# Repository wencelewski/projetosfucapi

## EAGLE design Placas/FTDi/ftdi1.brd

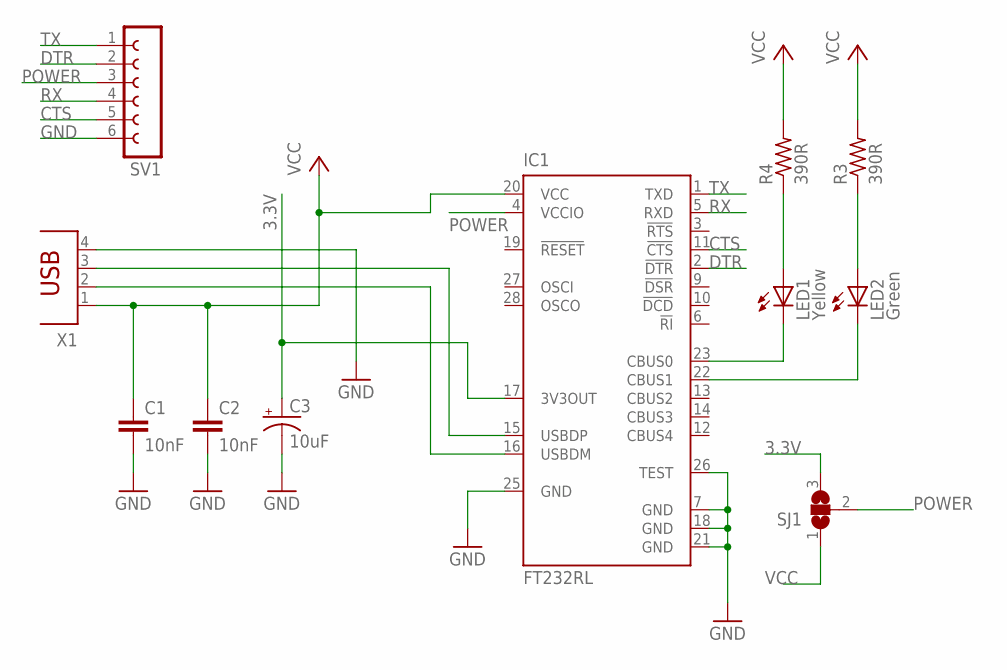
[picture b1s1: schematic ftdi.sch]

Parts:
C1, C2: 10nF; C0805
C3: 10uF; E2,5-6
IC1: FT232RL; SSOP28
LED1: Yellow; LED5MM
LED2: Green; LED5MM
R3, R4: 390R; R0805
SJ1: SJ2W; SJ_2
SV1: FE06-1; FE06
X1: PN87520

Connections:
3.3V: C3.+, IC1.17 (3V3OUT), SJ1.3
CTS: IC1.11 (!CTS), SV1.5
DTR: IC1.2 (!DTR), SV1.2
GND: C1.2, C2.2, C3.-, IC1.7 (GND), IC1.18 (GND), IC1.21 (GND), IC1.25 (GND), IC1.26 (TEST), SV1.6, X1.4
unnamed: IC1.23 (CBUS0), LED1.K (C)
unnamed: IC1.22 (CBUS1), LED2.K (C)
unnamed: LED2.A, R3.1
unnamed: LED1.A, R4.1
unnamed: IC1.16 (USBDM), X1.2
unnamed: IC1.15 (USBDP), X1.3
POWER: IC1.4 (VCCIO), SJ1.2, SV1.3
RX: IC1.5 (RXD), SV1.4
TX: IC1.1 (TXD), SV1.1
VCC: C1.1, C2.1, IC1.20 (VCC), R3.2, R4.2, SJ1.1, X1.1

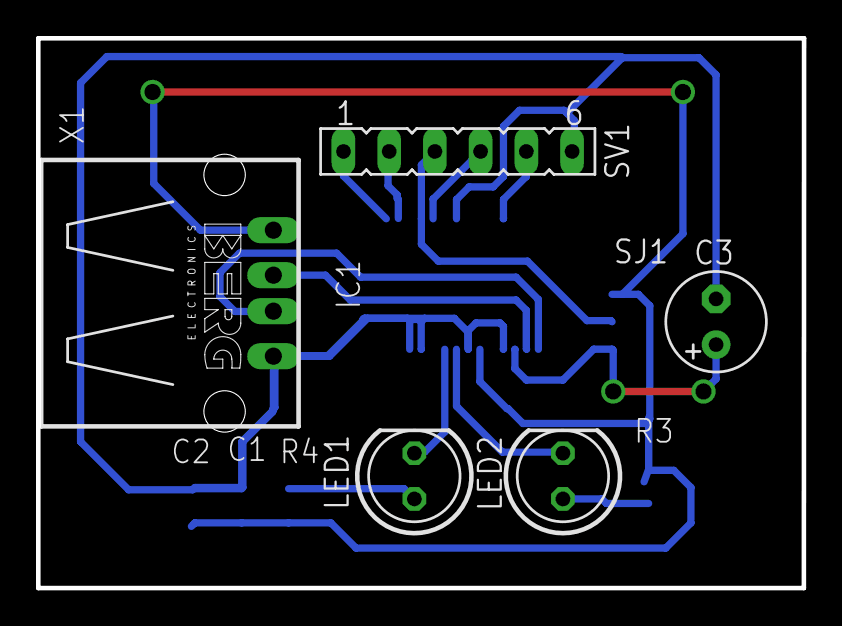
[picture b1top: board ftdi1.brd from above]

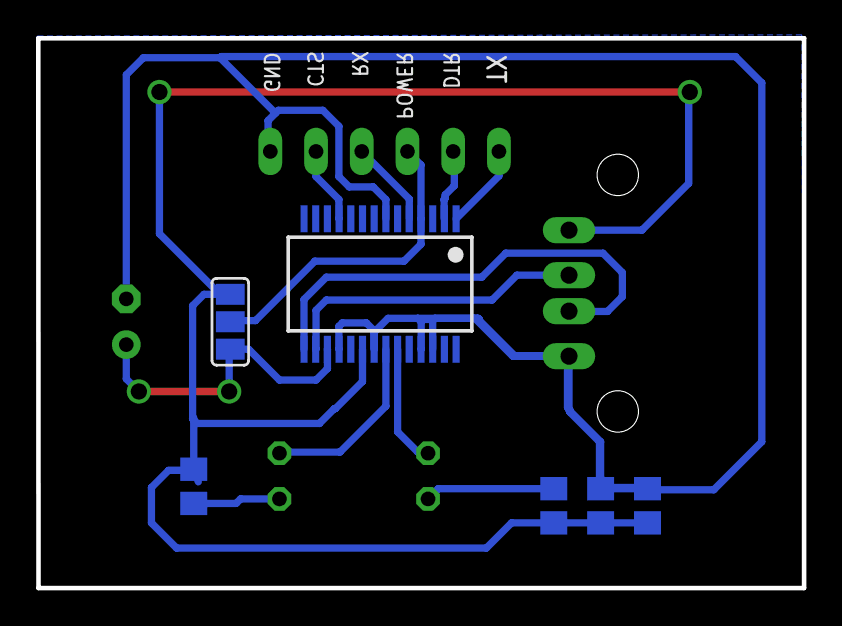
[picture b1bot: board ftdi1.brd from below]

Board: 2 copper layers, 42.5 x 30.5 mm, 11 parts (6 on the bottom side), 14 nets.

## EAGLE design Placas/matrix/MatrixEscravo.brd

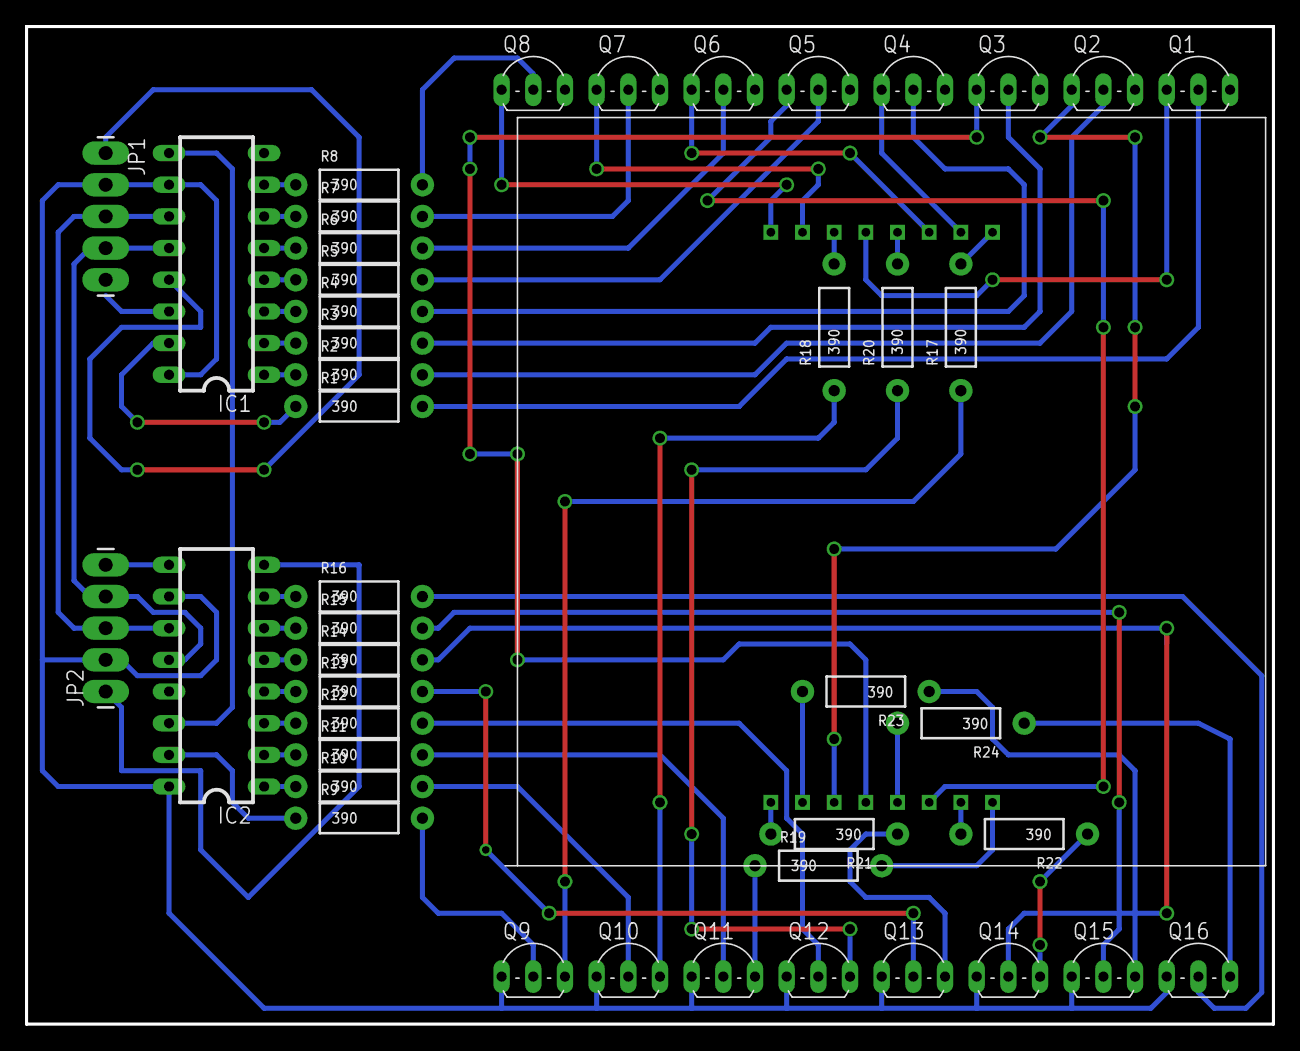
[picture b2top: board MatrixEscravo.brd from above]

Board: 2 copper layers, 100.0 x 80.0 mm, 45 parts (0 on the bottom side), 63 nets.

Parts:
IC1, IC2: 74LS595N; DIL16
JP1, JP2: 1X05_LONGPADS
Q1, Q2, Q3, Q4, Q5, Q6, Q7, Q8, Q9, Q10, Q11, Q12, Q13, Q14, Q15, Q16: BC548; TO92-EBC
R1, R2, R3, R4, R5, R6, R7, R8, R9, R10, R11, R12, R13, R14, R15, R16, R17, R18, R19, R20, R21, R22, R23, R24: 390; AXIAL-0.4
U$1: LEDMATRIX(HS2388); HS2388

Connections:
CLOCK: IC1.11, IC2.11, JP1.3, JP2.3
GND: IC1.8, IC1.13, IC2.8, IC2.13, JP1.1, JP2.1, Q1.E, Q2.E, Q3.E, Q4.E, Q5.E, Q6.E, Q7.E, Q8.E
LATCH: IC1.12, IC2.12, JP1.4, JP2.4
unnamed: Q1.B, R1.P$2
unnamed: IC1.15, R1.P$1
unnamed: Q8.B, R8.P$2
unnamed: IC1.1, R2.P$1
unnamed: Q16.E, R24.P$1
unnamed: Q15.E, R23.P$1
unnamed: Q14.E, R22.P$1
unnamed: IC1.2, R3.P$1
unnamed: IC1.3, R4.P$1
unnamed: IC1.4, R5.P$1
unnamed: IC1.5, R6.P$1
unnamed: IC1.6, R7.P$1
unnamed: IC1.7, R8.P$1
unnamed: Q13.E, R21.P$1
unnamed: Q2.B, R2.P$2
unnamed: Q4.B, R4.P$2
unnamed: Q5.B, R5.P$2
unnamed: Q6.B, R6.P$2
unnamed: Q7.B, R7.P$2
unnamed: Q1.C, U$1.13
unnamed: Q2.C, U$1.3
unnamed: Q3.B, R3.P$2
unnamed: Q4.C, U$1.10
unnamed: Q5.C, U$1.6
unnamed: Q6.C, U$1.11
unnamed: Q7.C, U$1.15
unnamed: Q8.C, U$1.16
unnamed: Q12.E, R20.P$1
unnamed: Q11.E, R19.P$1
unnamed: Q10.E, R18.P$1
unnamed: Q9.E, R17.P$1
unnamed: R17.P$2, U$1.9
unnamed: R18.P$2, U$1.14
unnamed: R19.P$2, U$1.8
unnamed: R20.P$2, U$1.12
unnamed: R21.P$2, U$1.1
unnamed: R22.P$2, U$1.7
unnamed: R23.P$2, U$1.2
unnamed: R24.P$2, U$1.5
unnamed: Q9.B, R9.P$2
unnamed: Q10.B, R10.P$2
unnamed: Q11.B, R11.P$2
unnamed: Q12.B, R12.P$2
unnamed: Q13.B, R13.P$2
unnamed: Q14.B, R14.P$2
unnamed: Q15.B, R15.P$2
unnamed: Q16.B, R16.P$2
unnamed: IC2.15, R9.P$1
unnamed: IC2.1, R10.P$1
unnamed: IC2.2, R11.P$1
unnamed: IC2.3, R12.P$1
unnamed: IC2.4, R13.P$1
unnamed: IC2.5, R14.P$1
unnamed: IC2.6, R15.P$1
unnamed: IC2.7, R16.P$1
unnamed: IC1.9, IC2.14
unnamed: Q3.C, U$1.4
QH: IC2.9, JP2.5
QH.: IC1.14, JP1.5
VCC: IC1.10, IC1.16, IC2.10, IC2.16, JP1.2, JP2.2, Q9.C, Q10.C, Q11.C, Q12.C, Q13.C, Q14.C, Q15.C, Q16.C

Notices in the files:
parts and their libraries:
SparkFun: Licensing: CC v3.0 Share-Alike You are welcome to use this library for commercial purposes.
